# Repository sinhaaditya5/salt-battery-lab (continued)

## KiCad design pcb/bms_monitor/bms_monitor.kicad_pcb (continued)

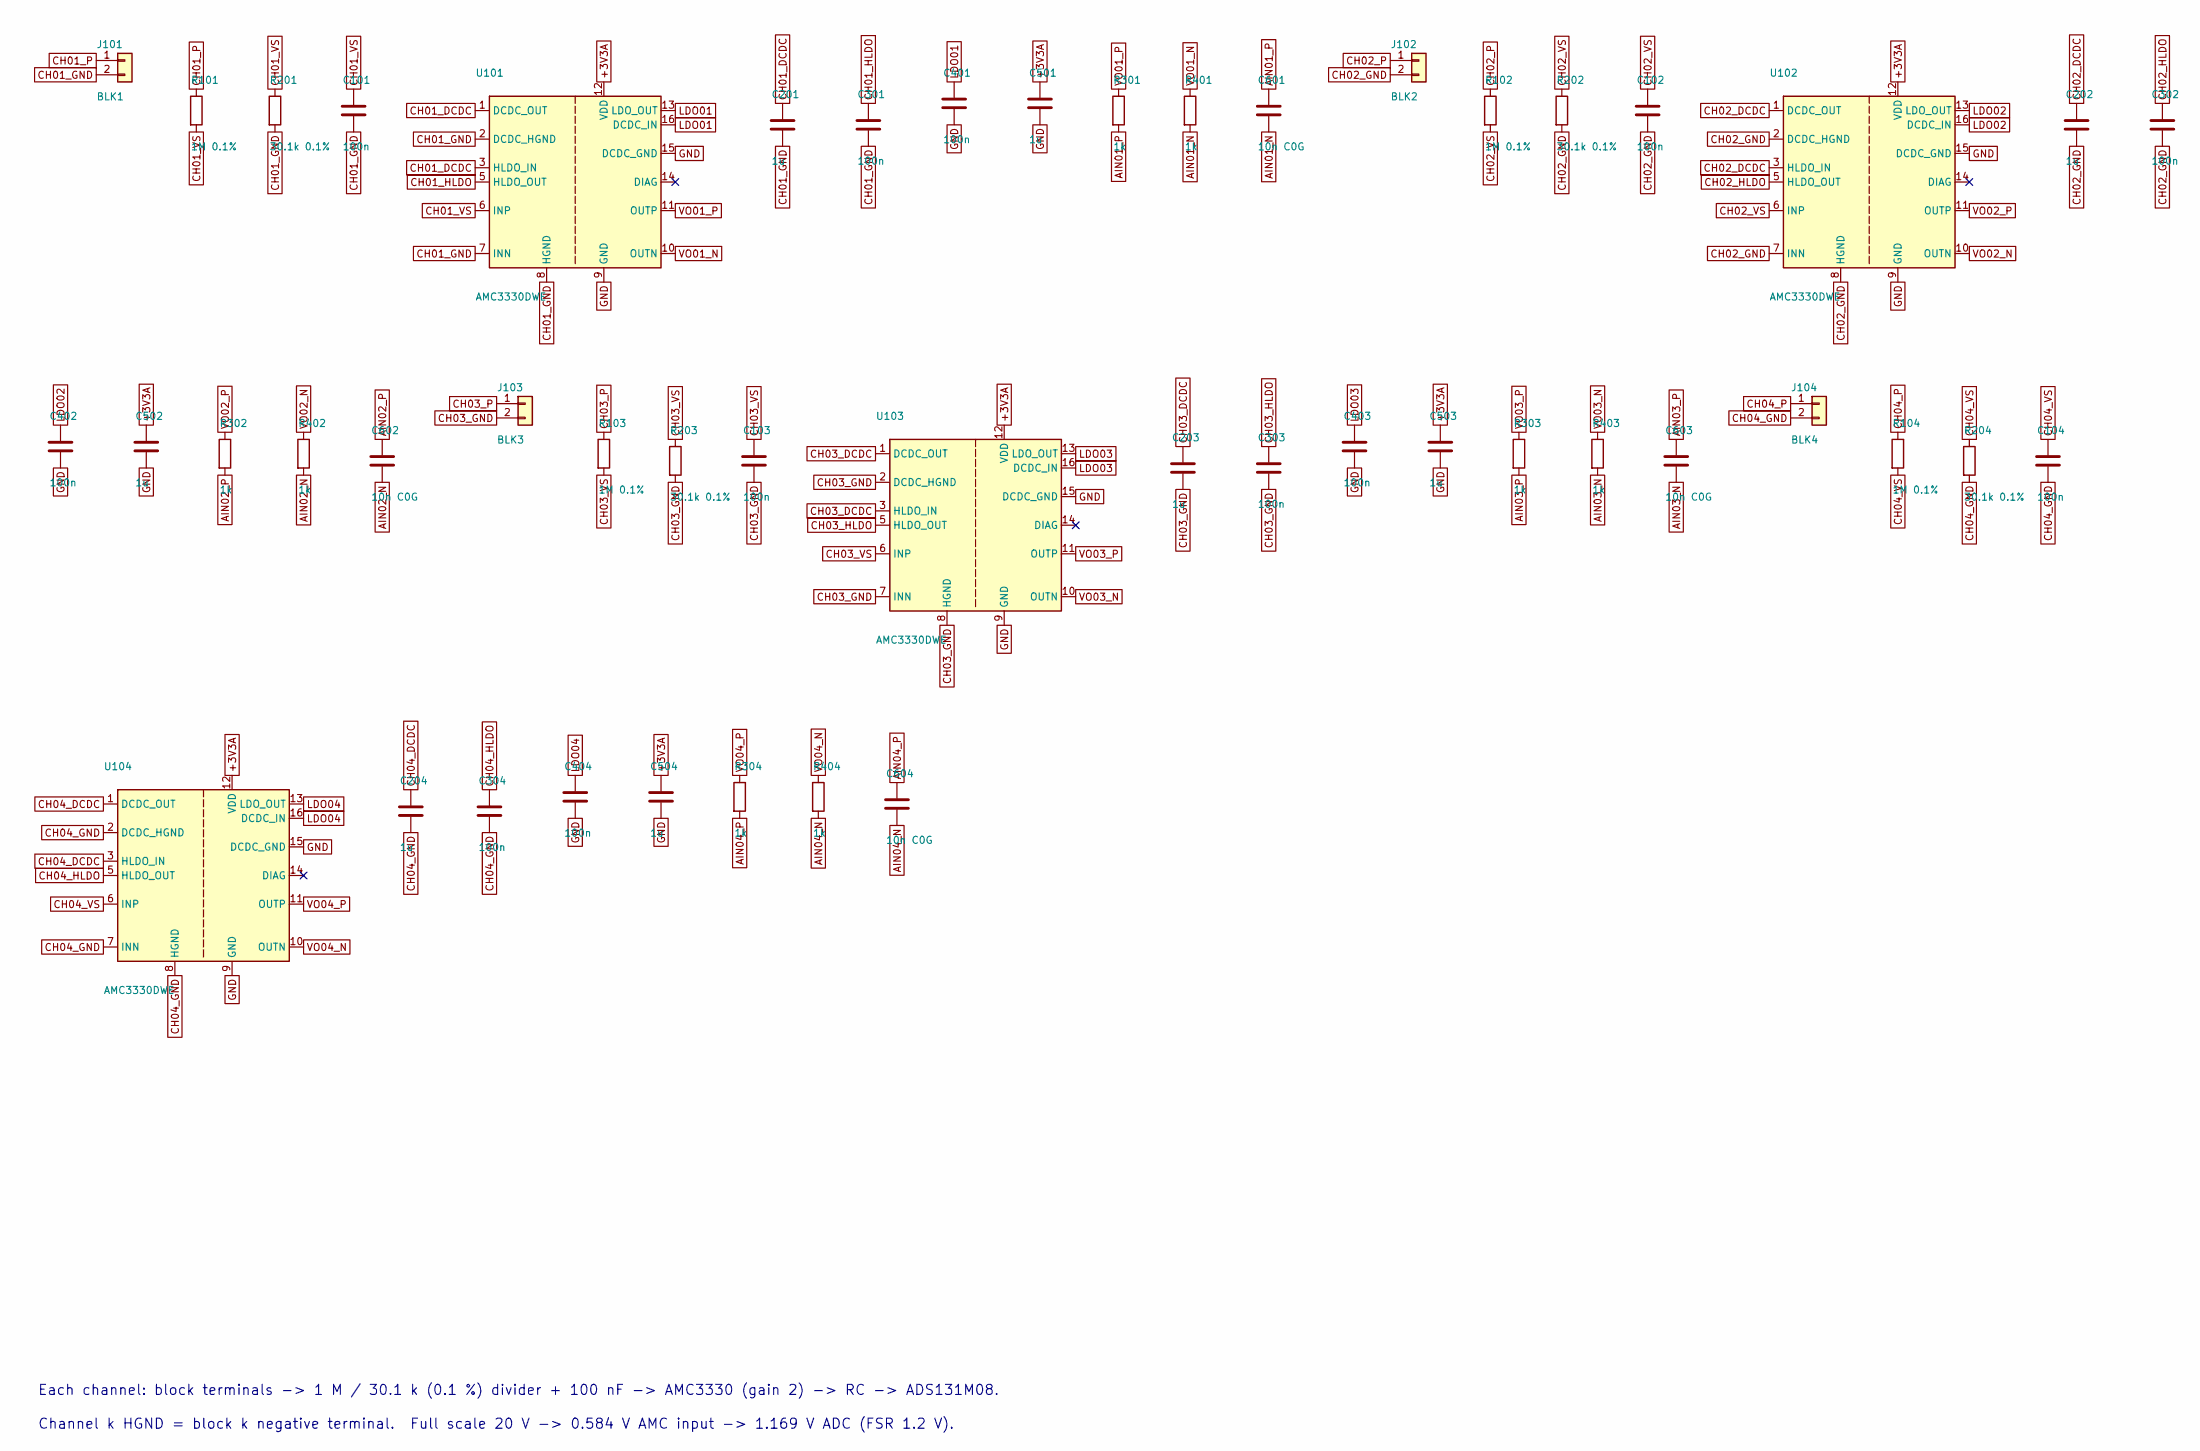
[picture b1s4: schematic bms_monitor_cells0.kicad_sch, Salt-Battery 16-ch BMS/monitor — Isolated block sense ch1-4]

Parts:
C101, C102, C103, C104, C301, C302, C303, C304, C401, C402, C403, C404: 100n; C_0603_1608Metric
C201, C202, C203, C204, C501, C502, C503, C504: 1u; C_0603_1608Metric
C601, C602, C603, C604: 10n C0G; C_0603_1608Metric
J101: BLK1; JST_XH_B2B-XH-A_1x02_P2.50mm_Vertical; MPN B2B-XH-A
J102: BLK2; JST_XH_B2B-XH-A_1x02_P2.50mm_Vertical; MPN B2B-XH-A
J103: BLK3; JST_XH_B2B-XH-A_1x02_P2.50mm_Vertical; MPN B2B-XH-A
J104: BLK4; JST_XH_B2B-XH-A_1x02_P2.50mm_Vertical; MPN B2B-XH-A
R101, R102, R103, R104: 1M 0.1%; R_1206_3216Metric
R201, R202, R203, R204: 30.1k 0.1%; R_0603_1608Metric
R301, R302, R303, R304, R401, R402, R403, R404: 1k; R_0603_1608Metric
U101, U102, U103, U104: AMC3330DWE; SOIC-16W_7.5x10.3mm_P1.27mm; MPN AMC3330DWER

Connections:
+3V3A: C501.1, C502.1, C503.1, C504.1, U101.12 (VDD), U102.12 (VDD), U103.12 (VDD), U104.12 (VDD); also elsewhere on the board
AIN01_N: C601.2, R401.2; also elsewhere on the board
AIN01_P: C601.1, R301.2; also elsewhere on the board
AIN02_N: C602.2, R402.2; also elsewhere on the board
AIN02_P: C602.1, R302.2; also elsewhere on the board
AIN03_N: C603.2, R403.2; also elsewhere on the board
AIN03_P: C603.1, R303.2; also elsewhere on the board
AIN04_N: C604.2, R404.2; also elsewhere on the board
AIN04_P: C604.1, R304.2; also elsewhere on the board
CH01_DCDC: C201.1, U101.1 (DCDC_OUT), U101.3 (HLDO_IN)
CH01_GND: C101.2, C201.2, C301.2, J101.2, R201.2, U101.2 (DCDC_HGND), U101.7 (INN), U101.8 (HGND)
CH01_HLDO: C301.1, U101.5 (HLDO_OUT)
CH01_P: J101.1, R101.1
CH01_VS: C101.1, R101.2, R201.1, U101.6 (INP)
CH02_DCDC: C202.1, U102.1 (DCDC_OUT), U102.3 (HLDO_IN)
CH02_GND: C102.2, C202.2, C302.2, J102.2, R202.2, U102.2 (DCDC_HGND), U102.7 (INN), U102.8 (HGND)
CH02_HLDO: C302.1, U102.5 (HLDO_OUT)
CH02_P: J102.1, R102.1
CH02_VS: C102.1, R102.2, R202.1, U102.6 (INP)
CH03_DCDC: C203.1, U103.1 (DCDC_OUT), U103.3 (HLDO_IN)
CH03_GND: C103.2, C203.2, C303.2, J103.2, R203.2, U103.2 (DCDC_HGND), U103.7 (INN), U103.8 (HGND)
CH03_HLDO: C303.1, U103.5 (HLDO_OUT)
CH03_P: J103.1, R103.1
CH03_VS: C103.1, R103.2, R203.1, U103.6 (INP)
CH04_DCDC: C204.1, U104.1 (DCDC_OUT), U104.3 (HLDO_IN)
CH04_GND: C104.2, C204.2, C304.2, J104.2, R204.2, U104.2 (DCDC_HGND), U104.7 (INN), U104.8 (HGND)
CH04_HLDO: C304.1, U104.5 (HLDO_OUT)
CH04_P: J104.1, R104.1
CH04_VS: C104.1, R104.2, R204.1, U104.6 (INP)
GND: C401.2, C402.2, C403.2, C404.2, C501.2, C502.2, C503.2, C504.2, U101.9 (GND), U101.15 (DCDC_GND), U102.9 (GND), U102.15 (DCDC_GND), U103.9 (GND), U103.15 (DCDC_GND), U104.9 (GND), U104.15 (DCDC_GND); also elsewhere on the board
LDO01: C401.1, U101.13 (LDO_OUT), U101.16 (DCDC_IN)
LDO02: C402.1, U102.13 (LDO_OUT), U102.16 (DCDC_IN)
LDO03: C403.1, U103.13 (LDO_OUT), U103.16 (DCDC_IN)
LDO04: C404.1, U104.13 (LDO_OUT), U104.16 (DCDC_IN)
VO01_N: R401.1, U101.10 (OUTN)
VO01_P: R301.1, U101.11 (OUTP)
VO02_N: R402.1, U102.10 (OUTN)
VO02_P: R302.1, U102.11 (OUTP)
VO03_N: R403.1, U103.10 (OUTN)
VO03_P: R303.1, U103.11 (OUTP)
VO04_N: R404.1, U104.10 (OUTN)
VO04_P: R304.1, U104.11 (OUTP)

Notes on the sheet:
Each channel: block terminals -> 1 M / 30.1 k (0.1 %) divider + 100 nF -> AMC3330 (gain 2) -> RC -> ADS131M08.
Channel k HGND = block k negative terminal. Full scale 20 V -> 0.584 V AMC input -> 1.169 V ADC (FSR 1.2 V).

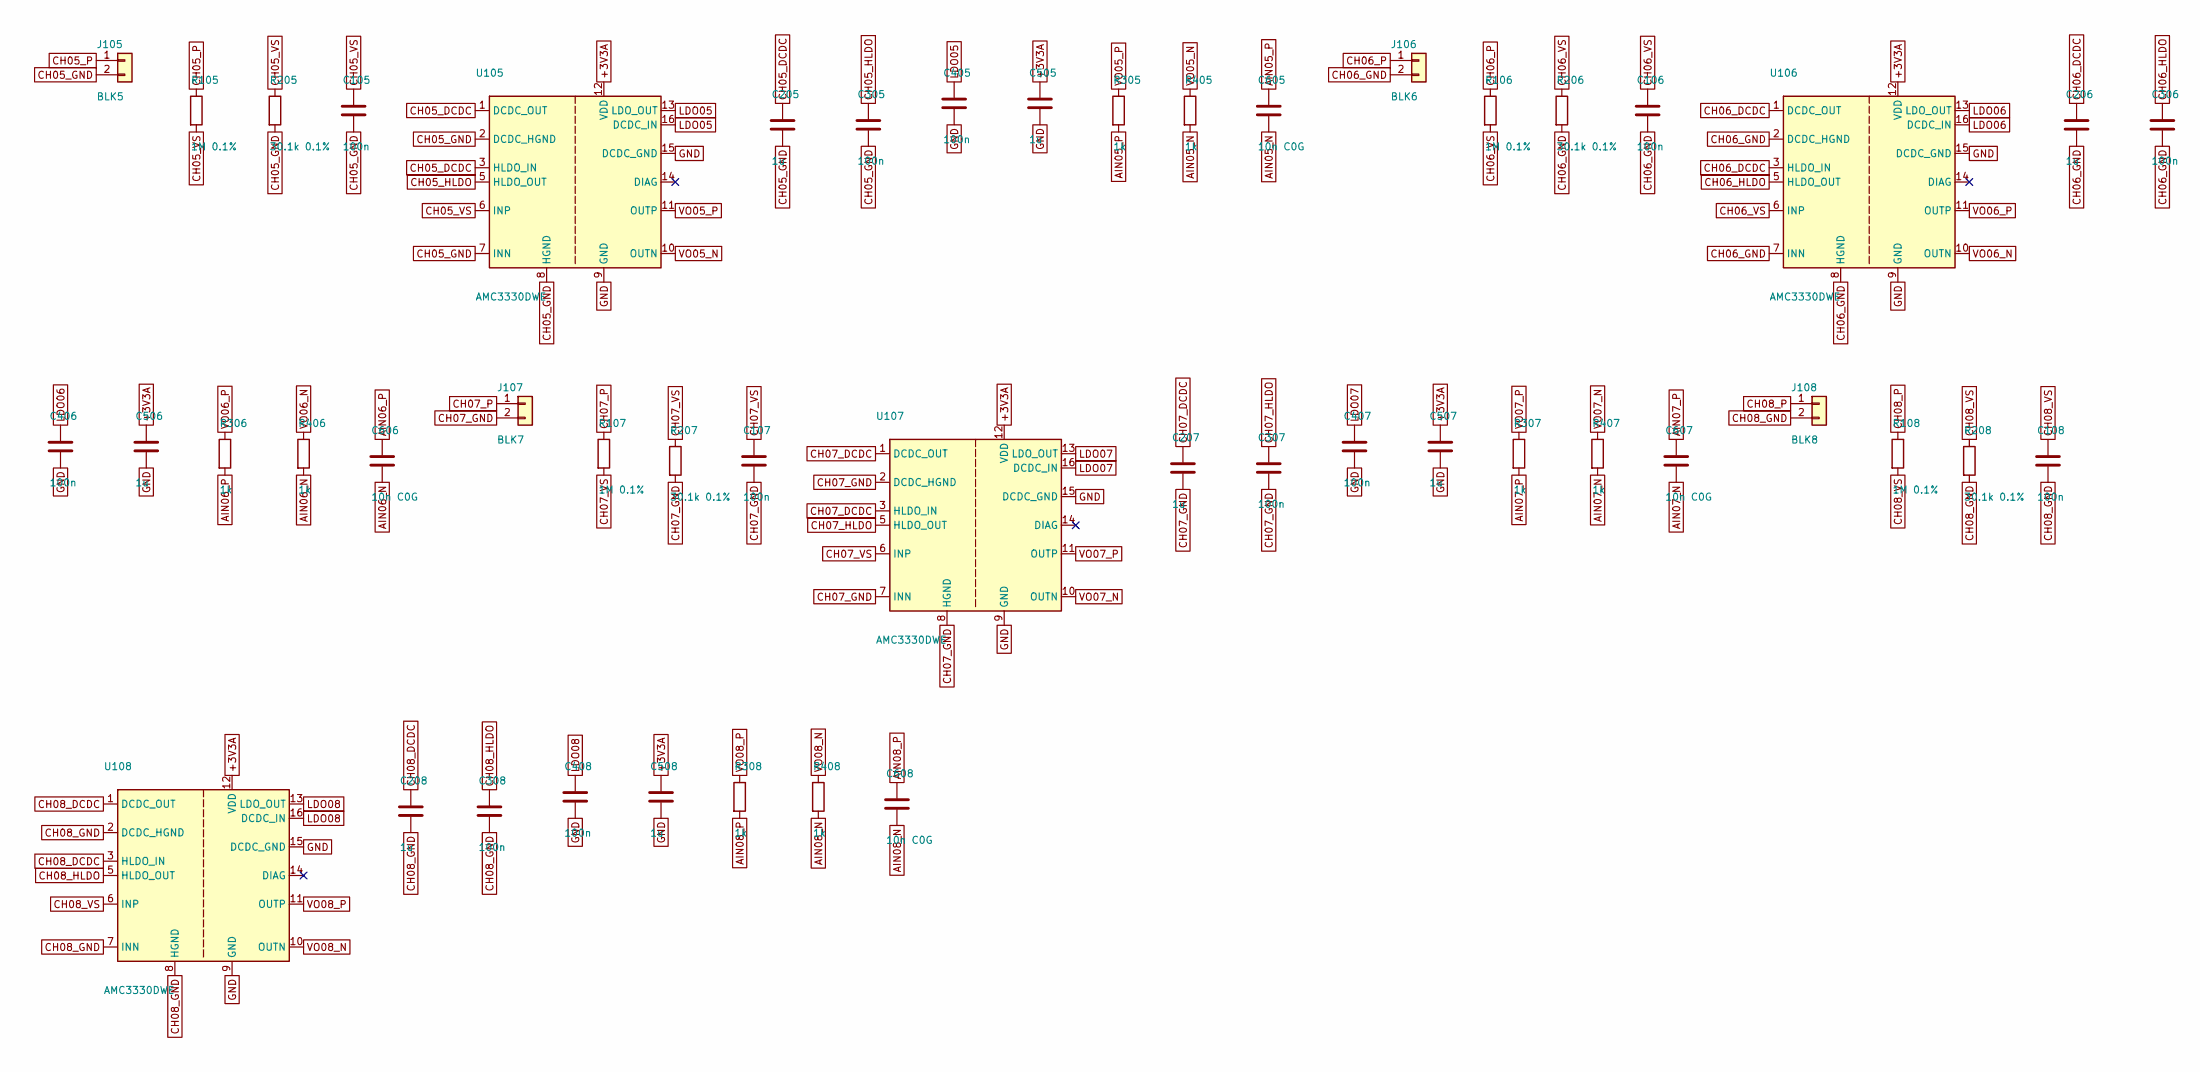
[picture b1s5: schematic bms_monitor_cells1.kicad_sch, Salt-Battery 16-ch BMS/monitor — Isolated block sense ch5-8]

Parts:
C105, C106, C107, C108, C305, C306, C307, C308, C405, C406, C407, C408: 100n; C_0603_1608Metric
C205, C206, C207, C208, C505, C506, C507, C508: 1u; C_0603_1608Metric
C605, C606, C607, C608: 10n C0G; C_0603_1608Metric
J105: BLK5; JST_XH_B2B-XH-A_1x02_P2.50mm_Vertical; MPN B2B-XH-A
J106: BLK6; JST_XH_B2B-XH-A_1x02_P2.50mm_Vertical; MPN B2B-XH-A
J107: BLK7; JST_XH_B2B-XH-A_1x02_P2.50mm_Vertical; MPN B2B-XH-A
J108: BLK8; JST_XH_B2B-XH-A_1x02_P2.50mm_Vertical; MPN B2B-XH-A
R105, R106, R107, R108: 1M 0.1%; R_1206_3216Metric
R205, R206, R207, R208: 30.1k 0.1%; R_0603_1608Metric
R305, R306, R307, R308, R405, R406, R407, R408: 1k; R_0603_1608Metric
U105, U106, U107, U108: AMC3330DWE; SOIC-16W_7.5x10.3mm_P1.27mm; MPN AMC3330DWER

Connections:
+3V3A: C505.1, C506.1, C507.1, C508.1, U105.12 (VDD), U106.12 (VDD), U107.12 (VDD), U108.12 (VDD); also elsewhere on the board
AIN05_N: C605.2, R405.2; also elsewhere on the board
AIN05_P: C605.1, R305.2; also elsewhere on the board
AIN06_N: C606.2, R406.2; also elsewhere on the board
AIN06_P: C606.1, R306.2; also elsewhere on the board
AIN07_N: C607.2, R407.2; also elsewhere on the board
AIN07_P: C607.1, R307.2; also elsewhere on the board
AIN08_N: C608.2, R408.2; also elsewhere on the board
AIN08_P: C608.1, R308.2; also elsewhere on the board
CH05_DCDC: C205.1, U105.1 (DCDC_OUT), U105.3 (HLDO_IN)
CH05_GND: C105.2, C205.2, C305.2, J105.2, R205.2, U105.2 (DCDC_HGND), U105.7 (INN), U105.8 (HGND)
CH05_HLDO: C305.1, U105.5 (HLDO_OUT)
CH05_P: J105.1, R105.1
CH05_VS: C105.1, R105.2, R205.1, U105.6 (INP)
CH06_DCDC: C206.1, U106.1 (DCDC_OUT), U106.3 (HLDO_IN)
CH06_GND: C106.2, C206.2, C306.2, J106.2, R206.2, U106.2 (DCDC_HGND), U106.7 (INN), U106.8 (HGND)
CH06_HLDO: C306.1, U106.5 (HLDO_OUT)
CH06_P: J106.1, R106.1
CH06_VS: C106.1, R106.2, R206.1, U106.6 (INP)
CH07_DCDC: C207.1, U107.1 (DCDC_OUT), U107.3 (HLDO_IN)
CH07_GND: C107.2, C207.2, C307.2, J107.2, R207.2, U107.2 (DCDC_HGND), U107.7 (INN), U107.8 (HGND)
CH07_HLDO: C307.1, U107.5 (HLDO_OUT)
CH07_P: J107.1, R107.1
CH07_VS: C107.1, R107.2, R207.1, U107.6 (INP)
CH08_DCDC: C208.1, U108.1 (DCDC_OUT), U108.3 (HLDO_IN)
CH08_GND: C108.2, C208.2, C308.2, J108.2, R208.2, U108.2 (DCDC_HGND), U108.7 (INN), U108.8 (HGND)
CH08_HLDO: C308.1, U108.5 (HLDO_OUT)
CH08_P: J108.1, R108.1
CH08_VS: C108.1, R108.2, R208.1, U108.6 (INP)
GND: C405.2, C406.2, C407.2, C408.2, C505.2, C506.2, C507.2, C508.2, U105.9 (GND), U105.15 (DCDC_GND), U106.9 (GND), U106.15 (DCDC_GND), U107.9 (GND), U107.15 (DCDC_GND), U108.9 (GND), U108.15 (DCDC_GND); also elsewhere on the board
LDO05: C405.1, U105.13 (LDO_OUT), U105.16 (DCDC_IN)
LDO06: C406.1, U106.13 (LDO_OUT), U106.16 (DCDC_IN)
LDO07: C407.1, U107.13 (LDO_OUT), U107.16 (DCDC_IN)
LDO08: C408.1, U108.13 (LDO_OUT), U108.16 (DCDC_IN)
VO05_N: R405.1, U105.10 (OUTN)
VO05_P: R305.1, U105.11 (OUTP)
VO06_N: R406.1, U106.10 (OUTN)
VO06_P: R306.1, U106.11 (OUTP)
VO07_N: R407.1, U107.10 (OUTN)
VO07_P: R307.1, U107.11 (OUTP)
VO08_N: R408.1, U108.10 (OUTN)
VO08_P: R308.1, U108.11 (OUTP)

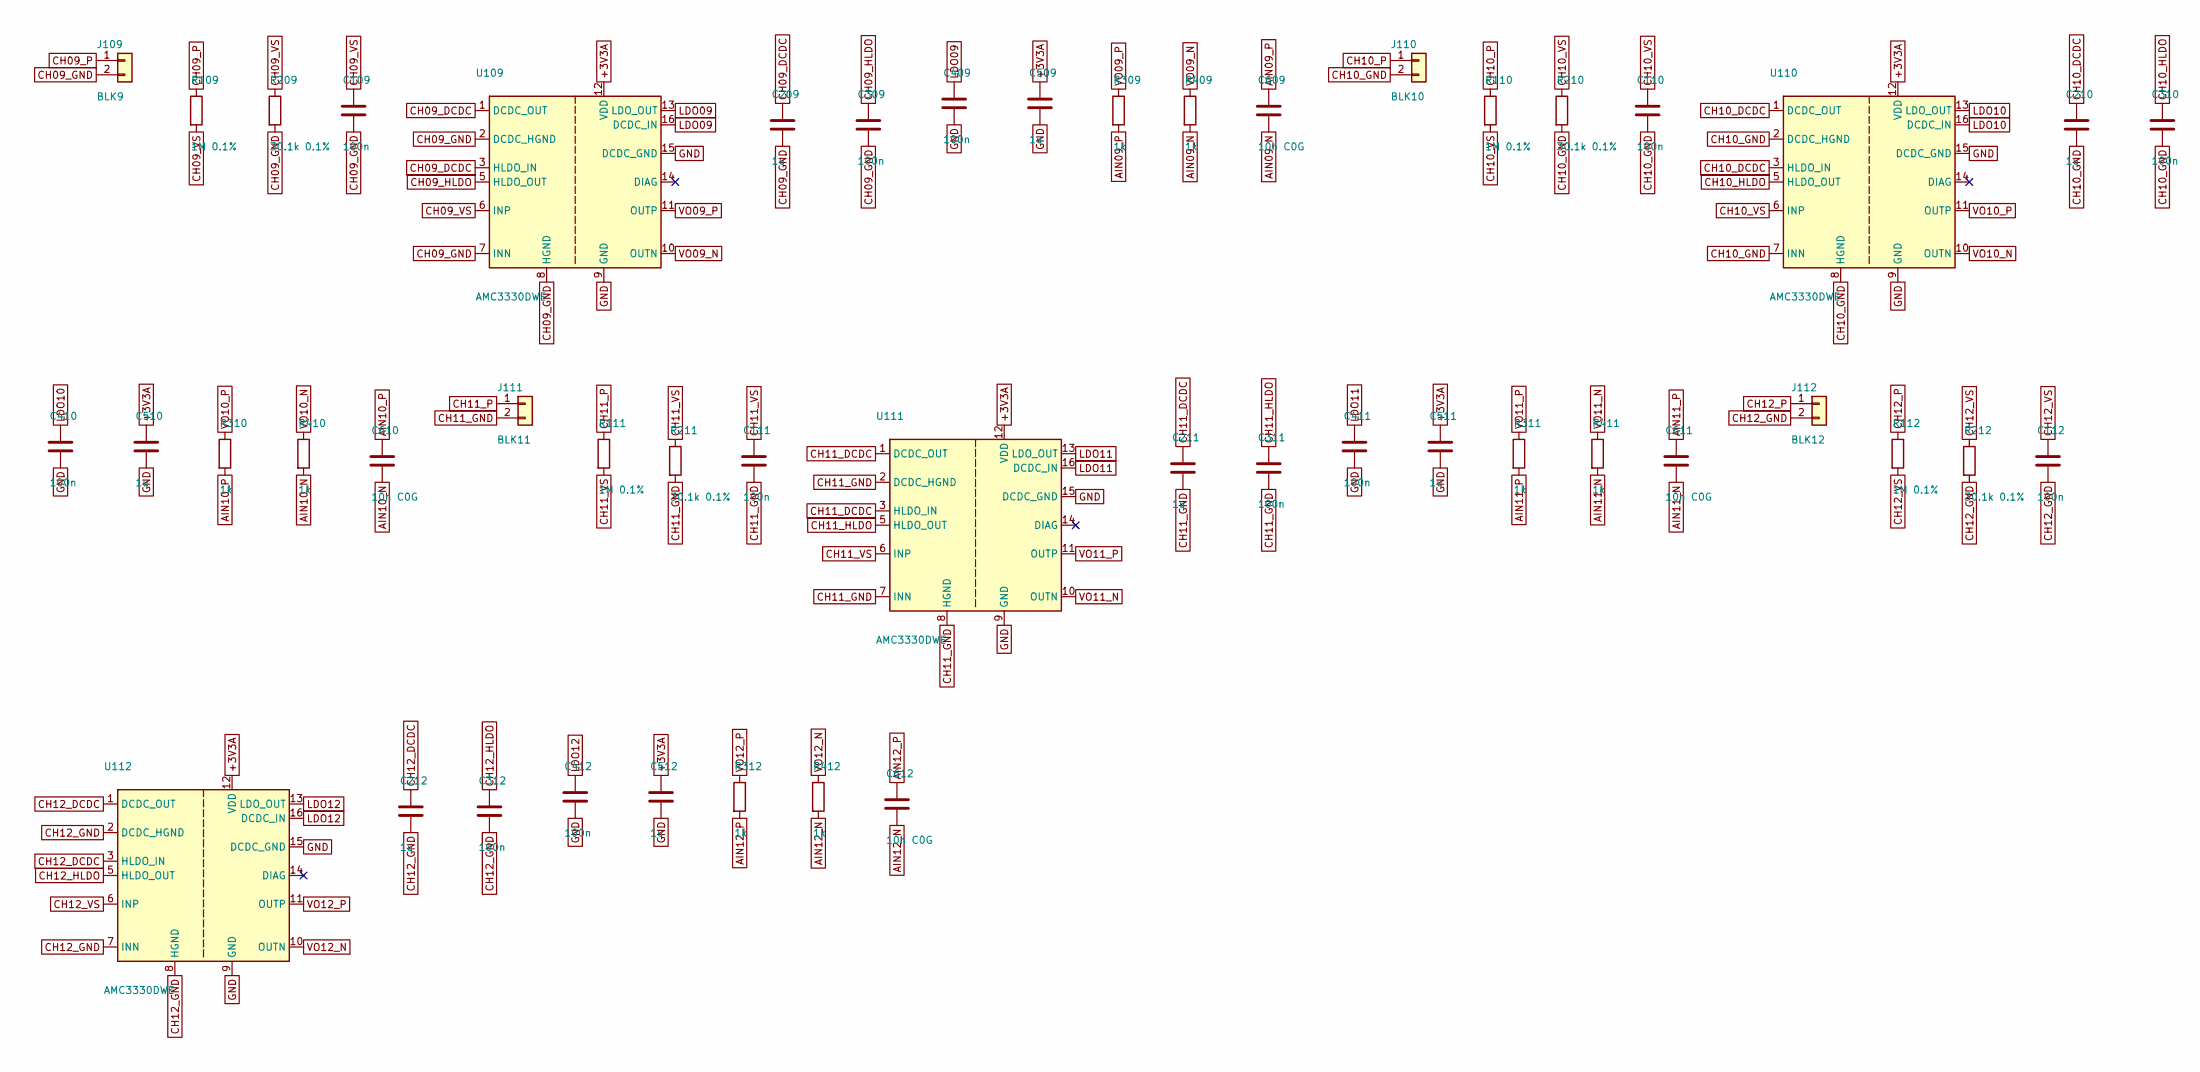
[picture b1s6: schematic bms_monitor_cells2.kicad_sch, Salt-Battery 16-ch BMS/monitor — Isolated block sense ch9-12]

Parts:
C109, C110, C111, C112, C309, C310, C311, C312, C409, C410, C411, C412: 100n; C_0603_1608Metric
C209, C210, C211, C212, C509, C510, C511, C512: 1u; C_0603_1608Metric
C609, C610, C611, C612: 10n C0G; C_0603_1608Metric
J109: BLK9; JST_XH_B2B-XH-A_1x02_P2.50mm_Vertical; MPN B2B-XH-A
J110: BLK10; JST_XH_B2B-XH-A_1x02_P2.50mm_Vertical; MPN B2B-XH-A
J111: BLK11; JST_XH_B2B-XH-A_1x02_P2.50mm_Vertical; MPN B2B-XH-A
J112: BLK12; JST_XH_B2B-XH-A_1x02_P2.50mm_Vertical; MPN B2B-XH-A
R109, R110, R111, R112: 1M 0.1%; R_1206_3216Metric
R209, R210, R211, R212: 30.1k 0.1%; R_0603_1608Metric
R309, R310, R311, R312, R409, R410, R411, R412: 1k; R_0603_1608Metric
U109, U110, U111, U112: AMC3330DWE; SOIC-16W_7.5x10.3mm_P1.27mm; MPN AMC3330DWER

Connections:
+3V3A: C509.1, C510.1, C511.1, C512.1, U109.12 (VDD), U110.12 (VDD), U111.12 (VDD), U112.12 (VDD); also elsewhere on the board
AIN09_N: C609.2, R409.2; also elsewhere on the board
AIN09_P: C609.1, R309.2; also elsewhere on the board
AIN10_N: C610.2, R410.2; also elsewhere on the board
AIN10_P: C610.1, R310.2; also elsewhere on the board
AIN11_N: C611.2, R411.2; also elsewhere on the board
AIN11_P: C611.1, R311.2; also elsewhere on the board
AIN12_N: C612.2, R412.2; also elsewhere on the board
AIN12_P: C612.1, R312.2; also elsewhere on the board
CH09_DCDC: C209.1, U109.1 (DCDC_OUT), U109.3 (HLDO_IN)
CH09_GND: C109.2, C209.2, C309.2, J109.2, R209.2, U109.2 (DCDC_HGND), U109.7 (INN), U109.8 (HGND)
CH09_HLDO: C309.1, U109.5 (HLDO_OUT)
CH09_P: J109.1, R109.1
CH09_VS: C109.1, R109.2, R209.1, U109.6 (INP)
CH10_DCDC: C210.1, U110.1 (DCDC_OUT), U110.3 (HLDO_IN)
CH10_GND: C110.2, C210.2, C310.2, J110.2, R210.2, U110.2 (DCDC_HGND), U110.7 (INN), U110.8 (HGND)
CH10_HLDO: C310.1, U110.5 (HLDO_OUT)
CH10_P: J110.1, R110.1
CH10_VS: C110.1, R110.2, R210.1, U110.6 (INP)
CH11_DCDC: C211.1, U111.1 (DCDC_OUT), U111.3 (HLDO_IN)
CH11_GND: C111.2, C211.2, C311.2, J111.2, R211.2, U111.2 (DCDC_HGND), U111.7 (INN), U111.8 (HGND)
CH11_HLDO: C311.1, U111.5 (HLDO_OUT)
CH11_P: J111.1, R111.1
CH11_VS: C111.1, R111.2, R211.1, U111.6 (INP)
CH12_DCDC: C212.1, U112.1 (DCDC_OUT), U112.3 (HLDO_IN)
CH12_GND: C112.2, C212.2, C312.2, J112.2, R212.2, U112.2 (DCDC_HGND), U112.7 (INN), U112.8 (HGND)
CH12_HLDO: C312.1, U112.5 (HLDO_OUT)
CH12_P: J112.1, R112.1
CH12_VS: C112.1, R112.2, R212.1, U112.6 (INP)
GND: C409.2, C410.2, C411.2, C412.2, C509.2, C510.2, C511.2, C512.2, U109.9 (GND), U109.15 (DCDC_GND), U110.9 (GND), U110.15 (DCDC_GND), U111.9 (GND), U111.15 (DCDC_GND), U112.9 (GND), U112.15 (DCDC_GND); also elsewhere on the board
LDO09: C409.1, U109.13 (LDO_OUT), U109.16 (DCDC_IN)
LDO10: C410.1, U110.13 (LDO_OUT), U110.16 (DCDC_IN)
LDO11: C411.1, U111.13 (LDO_OUT), U111.16 (DCDC_IN)
LDO12: C412.1, U112.13 (LDO_OUT), U112.16 (DCDC_IN)
VO09_N: R409.1, U109.10 (OUTN)
VO09_P: R309.1, U109.11 (OUTP)
VO10_N: R410.1, U110.10 (OUTN)
VO10_P: R310.1, U110.11 (OUTP)
VO11_N: R411.1, U111.10 (OUTN)
VO11_P: R311.1, U111.11 (OUTP)
VO12_N: R412.1, U112.10 (OUTN)
VO12_P: R312.1, U112.11 (OUTP)

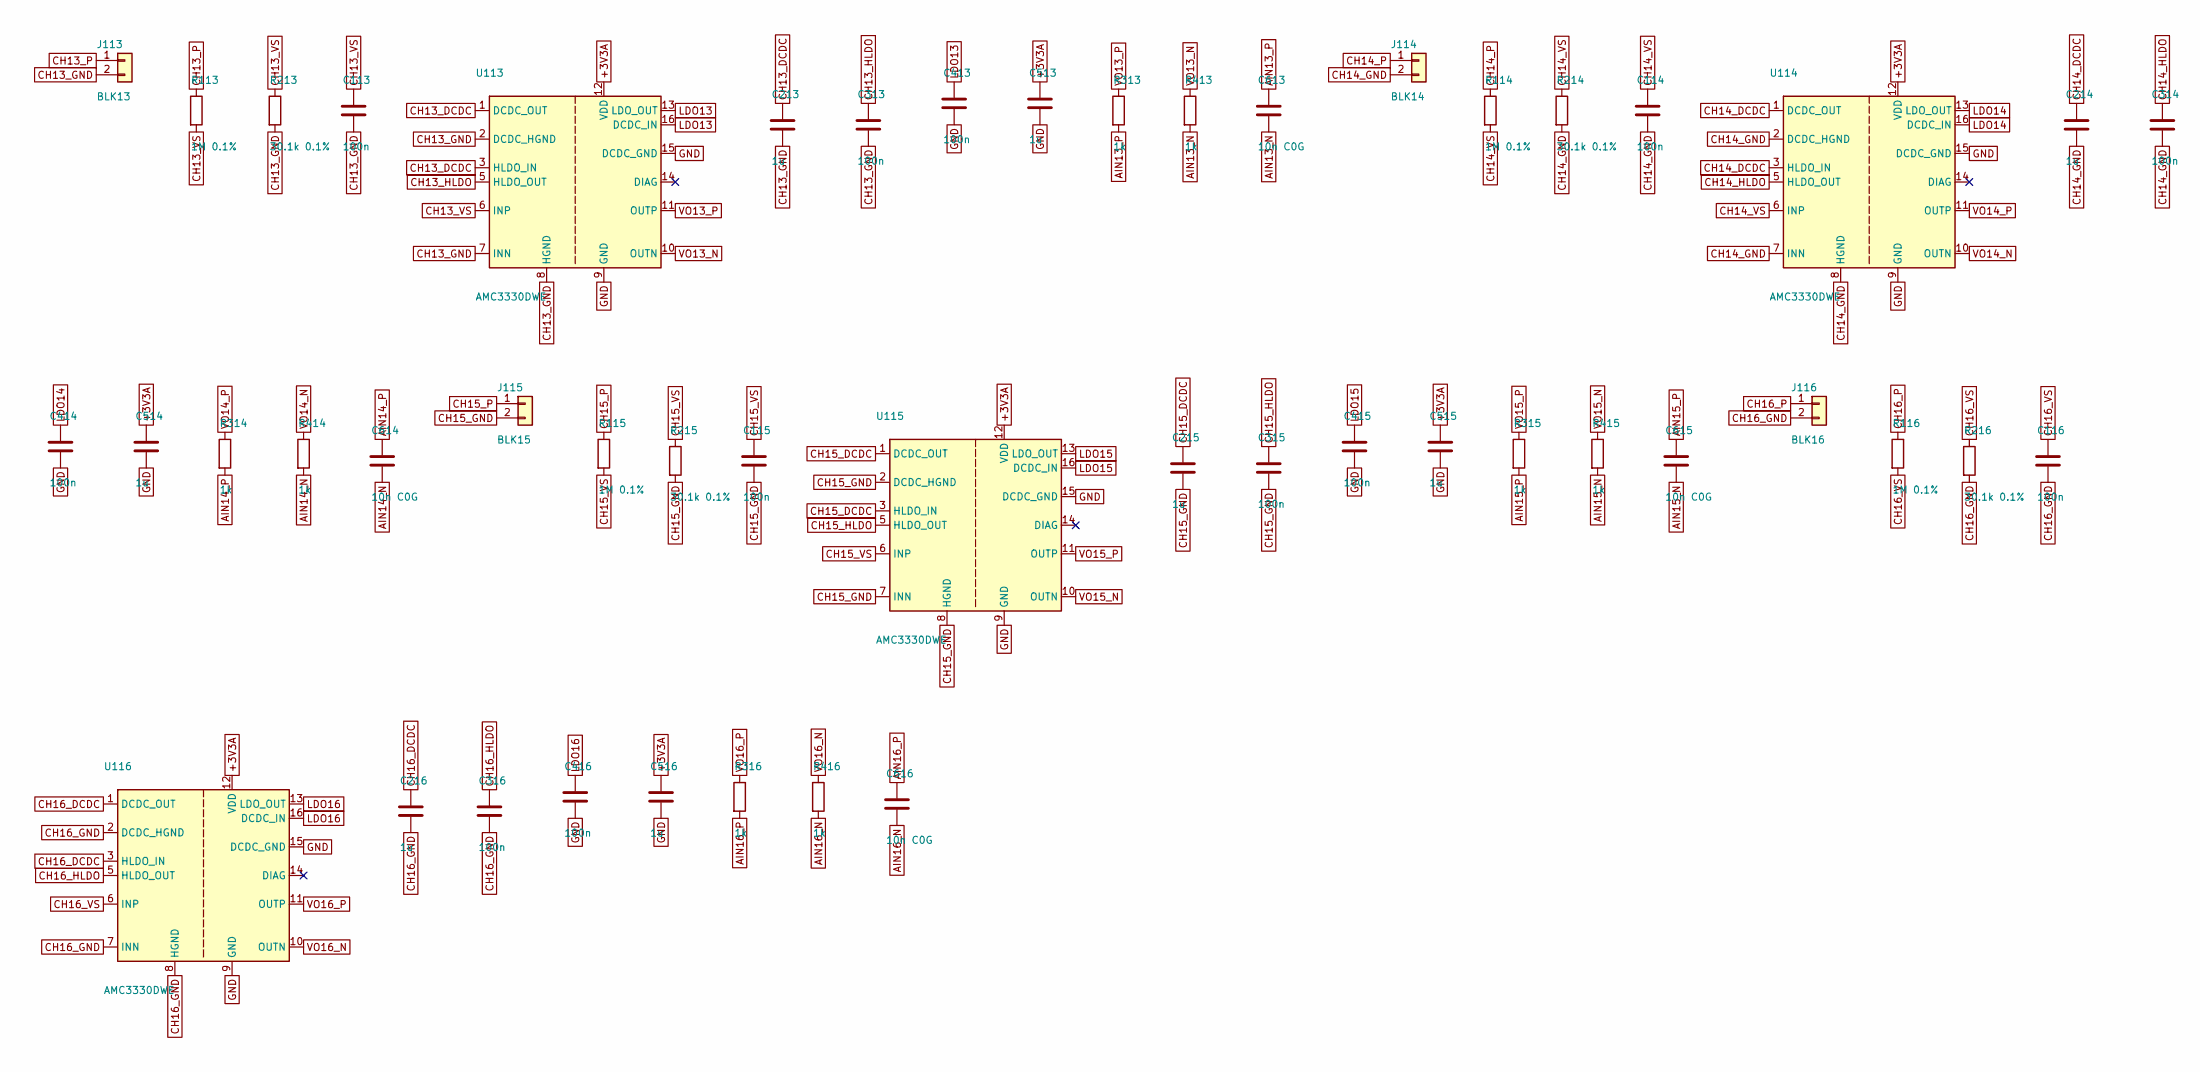
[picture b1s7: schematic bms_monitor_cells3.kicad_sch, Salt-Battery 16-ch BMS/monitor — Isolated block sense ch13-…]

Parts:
C113, C114, C115, C116, C313, C314, C315, C316, C413, C414, C415, C416: 100n; C_0603_1608Metric
C213, C214, C215, C216, C513, C514, C515, C516: 1u; C_0603_1608Metric
C613, C614, C615, C616: 10n C0G; C_0603_1608Metric
J113: BLK13; JST_XH_B2B-XH-A_1x02_P2.50mm_Vertical; MPN B2B-XH-A
J114: BLK14; JST_XH_B2B-XH-A_1x02_P2.50mm_Vertical; MPN B2B-XH-A
J115: BLK15; JST_XH_B2B-XH-A_1x02_P2.50mm_Vertical; MPN B2B-XH-A
J116: BLK16; JST_XH_B2B-XH-A_1x02_P2.50mm_Vertical; MPN B2B-XH-A
R113, R114, R115, R116: 1M 0.1%; R_1206_3216Metric
R213, R214, R215, R216: 30.1k 0.1%; R_0603_1608Metric
R313, R314, R315, R316, R413, R414, R415, R416: 1k; R_0603_1608Metric
U113, U114, U115, U116: AMC3330DWE; SOIC-16W_7.5x10.3mm_P1.27mm; MPN AMC3330DWER

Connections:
+3V3A: C513.1, C514.1, C515.1, C516.1, U113.12 (VDD), U114.12 (VDD), U115.12 (VDD), U116.12 (VDD); also elsewhere on the board
AIN13_N: C613.2, R413.2; also elsewhere on the board
AIN13_P: C613.1, R313.2; also elsewhere on the board
AIN14_N: C614.2, R414.2; also elsewhere on the board
AIN14_P: C614.1, R314.2; also elsewhere on the board
AIN15_N: C615.2, R415.2; also elsewhere on the board
AIN15_P: C615.1, R315.2; also elsewhere on the board
AIN16_N: C616.2, R416.2; also elsewhere on the board
AIN16_P: C616.1, R316.2; also elsewhere on the board
CH13_DCDC: C213.1, U113.1 (DCDC_OUT), U113.3 (HLDO_IN)
CH13_GND: C113.2, C213.2, C313.2, J113.2, R213.2, U113.2 (DCDC_HGND), U113.7 (INN), U113.8 (HGND)
CH13_HLDO: C313.1, U113.5 (HLDO_OUT)
CH13_P: J113.1, R113.1
CH13_VS: C113.1, R113.2, R213.1, U113.6 (INP)
CH14_DCDC: C214.1, U114.1 (DCDC_OUT), U114.3 (HLDO_IN)
CH14_GND: C114.2, C214.2, C314.2, J114.2, R214.2, U114.2 (DCDC_HGND), U114.7 (INN), U114.8 (HGND)
CH14_HLDO: C314.1, U114.5 (HLDO_OUT)
CH14_P: J114.1, R114.1
CH14_VS: C114.1, R114.2, R214.1, U114.6 (INP)
CH15_DCDC: C215.1, U115.1 (DCDC_OUT), U115.3 (HLDO_IN)
CH15_GND: C115.2, C215.2, C315.2, J115.2, R215.2, U115.2 (DCDC_HGND), U115.7 (INN), U115.8 (HGND)
CH15_HLDO: C315.1, U115.5 (HLDO_OUT)
CH15_P: J115.1, R115.1
CH15_VS: C115.1, R115.2, R215.1, U115.6 (INP)
CH16_DCDC: C216.1, U116.1 (DCDC_OUT), U116.3 (HLDO_IN)
CH16_GND: C116.2, C216.2, C316.2, J116.2, R216.2, U116.2 (DCDC_HGND), U116.7 (INN), U116.8 (HGND)
CH16_HLDO: C316.1, U116.5 (HLDO_OUT)
CH16_P: J116.1, R116.1
CH16_VS: C116.1, R116.2, R216.1, U116.6 (INP)
GND: C413.2, C414.2, C415.2, C416.2, C513.2, C514.2, C515.2, C516.2, U113.9 (GND), U113.15 (DCDC_GND), U114.9 (GND), U114.15 (DCDC_GND), U115.9 (GND), U115.15 (DCDC_GND), U116.9 (GND), U116.15 (DCDC_GND); also elsewhere on the board
LDO13: C413.1, U113.13 (LDO_OUT), U113.16 (DCDC_IN)
LDO14: C414.1, U114.13 (LDO_OUT), U114.16 (DCDC_IN)
LDO15: C415.1, U115.13 (LDO_OUT), U115.16 (DCDC_IN)
LDO16: C416.1, U116.13 (LDO_OUT), U116.16 (DCDC_IN)
VO13_N: R413.1, U113.10 (OUTN)
VO13_P: R313.1, U113.11 (OUTP)
VO14_N: R414.1, U114.10 (OUTN)
VO14_P: R314.1, U114.11 (OUTP)
VO15_N: R415.1, U115.10 (OUTN)
VO15_P: R315.1, U115.11 (OUTP)
VO16_N: R416.1, U116.10 (OUTN)
VO16_P: R316.1, U116.11 (OUTP)

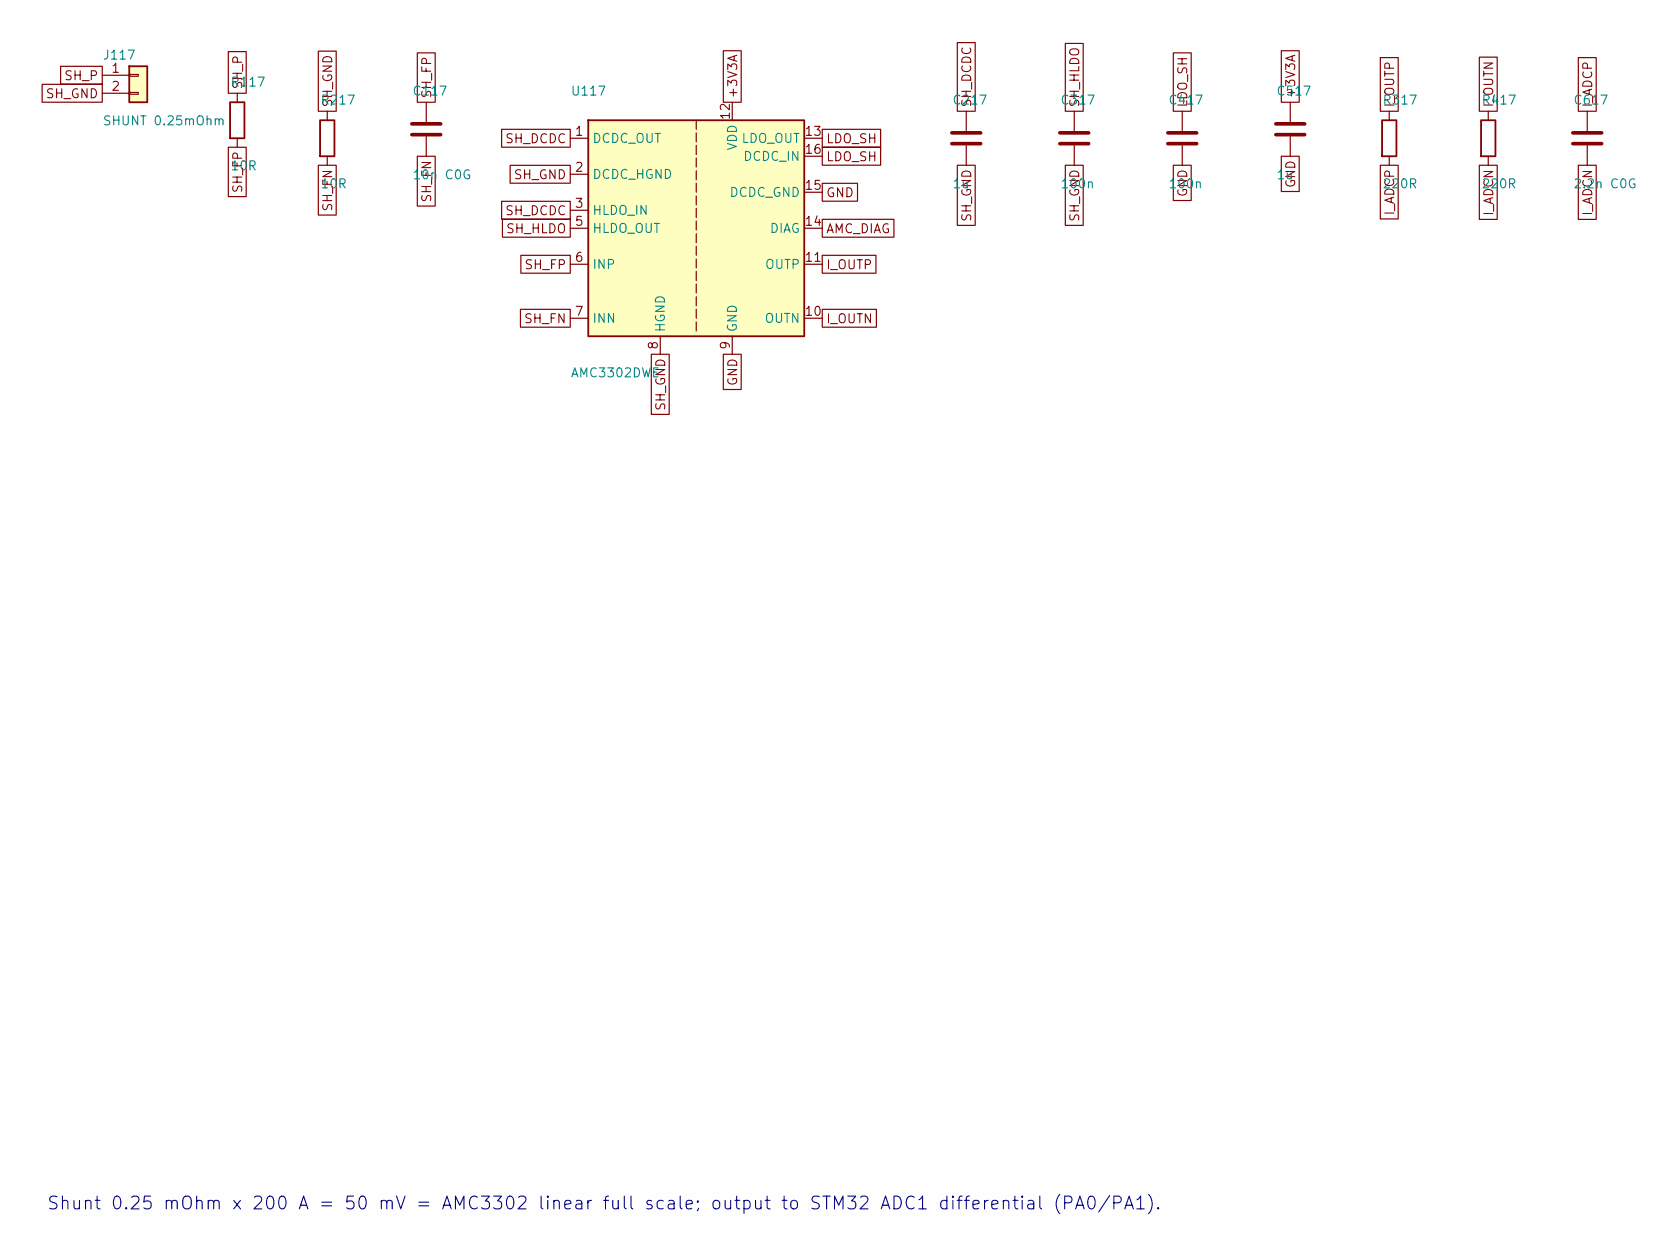
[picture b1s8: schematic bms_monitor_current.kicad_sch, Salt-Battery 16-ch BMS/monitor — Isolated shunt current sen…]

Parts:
C117: 10n C0G; C_0603_1608Metric
C217, C517: 1u; C_0603_1608Metric
C317, C417: 100n; C_0603_1608Metric
C617: 2.2n C0G; C_0603_1608Metric
J117: SHUNT 0.25mOhm; JST_XH_B2B-XH-A_1x02_P2.50mm_Vertical; MPN B2B-XH-A
R117, R217: 10R; R_0603_1608Metric
R317, R417: 220R; R_0603_1608Metric
U117: AMC3302DWE; SOIC-16W_7.5x10.3mm_P1.27mm; MPN AMC3302DWER

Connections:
+3V3A: C517.1, U117.12 (VDD); also elsewhere on the board
AMC_DIAG: U117.14 (DIAG); also elsewhere on the board
GND: C417.2, C517.2, U117.9 (GND), U117.15 (DCDC_GND); also elsewhere on the board
I_ADCN: C617.2, R417.2; also elsewhere on the board
I_ADCP: C617.1, R317.2; also elsewhere on the board
I_OUTN: R417.1, U117.10 (OUTN)
I_OUTP: R317.1, U117.11 (OUTP)
LDO_SH: C417.1, U117.13 (LDO_OUT), U117.16 (DCDC_IN)
SH_DCDC: C217.1, U117.1 (DCDC_OUT), U117.3 (HLDO_IN)
SH_FN: C117.2, R217.2, U117.7 (INN)
SH_FP: C117.1, R117.2, U117.6 (INP)
SH_GND: C217.2, C317.2, J117.2, R217.1, U117.2 (DCDC_HGND), U117.8 (HGND)
SH_HLDO: C317.1, U117.5 (HLDO_OUT)
SH_P: J117.1, R117.1

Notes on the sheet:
Shunt 0.25 mOhm x 200 A = 50 mV = AMC3302 linear full scale; output to STM32 ADC1 differential (PA0/PA1).

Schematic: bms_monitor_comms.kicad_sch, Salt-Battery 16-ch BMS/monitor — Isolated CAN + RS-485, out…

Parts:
C49, C52, C55, C57: 10u; C_0805_2012Metric
C50, C51, C53, C56, C58, C59: 100n; C_0603_1608Metric
C54: 4.7n; C_0603_1608Metric
D6: NUP2105L; SOT-23; MPN NUP2105LT1G
D7: SM712; SOT-23; MPN SM712.TCT
D8: STPS2H100A; D_SMA; MPN STPS2H100A
J5, J6: CAN; PhoenixContact_MC_1,5_3-G-3.5_1x03_P3.50mm_Horizontal; MPN 1803280
J7, J8: RS485; PhoenixContact_MC_1,5_3-G-3.5_1x03_P3.50mm_Horizontal; MPN 1803280
J9: CONTACTOR; TerminalBlock_Phoenix_MKDS-1,5-2-5.08_1x02_P5.08mm_Horizont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; MPN 1715721
J10: ALARM; TerminalBlock_Phoenix_MKDS-1,5-3-5.08_1x03_P5.08mm_Horizont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; MPN 1715734
JP1, JP2: TERM; SolderJumper-2_P1.3mm_Open_RoundedPad1.0x1.5mm
K1: G5V-1-DC5; Relay_SPDT_Omron_G5V-1; MPN G5V-1 DC5
Q1: DMN10H220L; SOT-23; MPN DMN10H220L-7
R42, R43, R46: 10k; R_0603_1608Metric
R44, R45: 60.4R; R_0603_1608Metric
R47: 120R; R_1206_3216Metric
R48, R50: 100k; R_0603_1608Metric
R49: 100R; R_0603_1608Metric
U7: ISOW1044DFMR; SOIC-20W_7.5x12.8mm_P1.27mm; MPN ISOW1044DFMR
U8: ADM2687EBRIZ; SOIC-16W_7.5x12.8mm_P1.27mm; MPN ADM2687EBRIZ
U9: 74AHCT1G125; SOT-23-5; MPN 74AHCT1G125GW
U10: TPL7407LAD; SOIC-16_3.9x9.9mm_P1.27mm; MPN TPL7407LADR

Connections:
+3V3: C51.1, C55.1, C56.1, R42.2, R43.2, U7.1 (VIO), U8.2 (VCC), U8.7 (VCC); also elsewhere on the board
+5V: C49.1, C50.1, C59.1, K1.2, U7.9 (VDD), U9.5 (VCC), U10.9 (COM); also elsewhere on the board
ALARM_EN: U10.1 (IN1); also elsewhere on the board
ALM_COM: J10.2, K1.5, K1.6
ALM_NC: J10.3, K1.1
ALM_NO: J10.1, K1.10
CAN_FLT: R43.1, U7.8 (EN/FLT); also elsewhere on the board
CAN_RX: U7.5 (RXD); also elsewhere on the board
CAN_STB: R42.1, U7.4 (STB); also elsewhere on the board
CAN_TX: U7.3 (TXD); also elsewhere on the board
CONT_DRV: R49.1, U9.4
CONT_EN: R48.1, U9.2; also elsewhere on the board
CONT_G: Q1.1 (G), R49.2, R50.1
CONT_OUT: D8.2 (A), J9.2, Q1.3 (D)
GND: C49.2, C50.2, C51.2, C55.2, C56.2, C59.2, Q1.2 (S), R46.2, R48.2, R50.2, U7.2 (IN), U7.6 (GNDIO), U7.10 (GND1), U8.1 (GND1), U8.8 (GND1), U9.1, U9.3 (GND), U10.2 (IN2), U10.3 (IN3), U10.4 (IN4), U10.5 (IN5), U10.6 (IN6), U10.7 (IN7), U10.8 (GND); also elsewhere on the board
I485_A: D7.1 (A1), J7.1, J8.1, JP2.1 (A), U8.11 (Y), U8.14 (A)
I485_B: D7.2 (A2), J7.2, J8.2, R47.2, U8.12 (Z), U8.13 (B)
I485_GND: C57.2, C58.2, D7.3 (common), J7.3, J8.3, U8.9 (GND2), U8.16 (GND2)
I485_TERM: JP2.2 (B), R47.1
I485_VISO: C57.1, C58.1, U8.10 (VISOOUT), U8.15 (VISOIN)
ICAN_GND: C52.2, C53.2, C54.2, D6.3 (A), J5.3, J6.3, U7.11 (GND2), U7.15 (GISOIN), U7.16 (GISOIN), U7.17 (GISOIN)
ICAN_H: D6.1 (K), J5.1, J6.1, JP1.1 (A), U7.19 (CANH)
ICAN_L: D6.2 (K), J5.2, J6.2, R45.2, U7.18 (CANL)
ICAN_SPLIT: C54.1, R44.2, R45.1
ICAN_TERM: JP1.2 (B), R44.1
ICAN_VISO: C52.1, C53.1, U7.12 (VISOOUT), U7.13 (VSIN), U7.20 (VISOIN)
RLY_COIL: K1.9, U10.16 (OUT1)
RS485_DE: R46.1, U8.4 (~RE), U8.5 (DE); also elsewhere on the board
RS485_RX: U8.3 (RXD); also elsewhere on the board
RS485_TX: U8.6 (TXD); also elsewhere on the board
VIN_P: D8.1 (K), J9.1; also elsewhere on the board
